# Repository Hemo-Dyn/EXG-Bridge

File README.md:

# EXG-Bridge
Ongoing development for ECG and EMG hardware interfacing with iPhones to present heartrate and muscular data

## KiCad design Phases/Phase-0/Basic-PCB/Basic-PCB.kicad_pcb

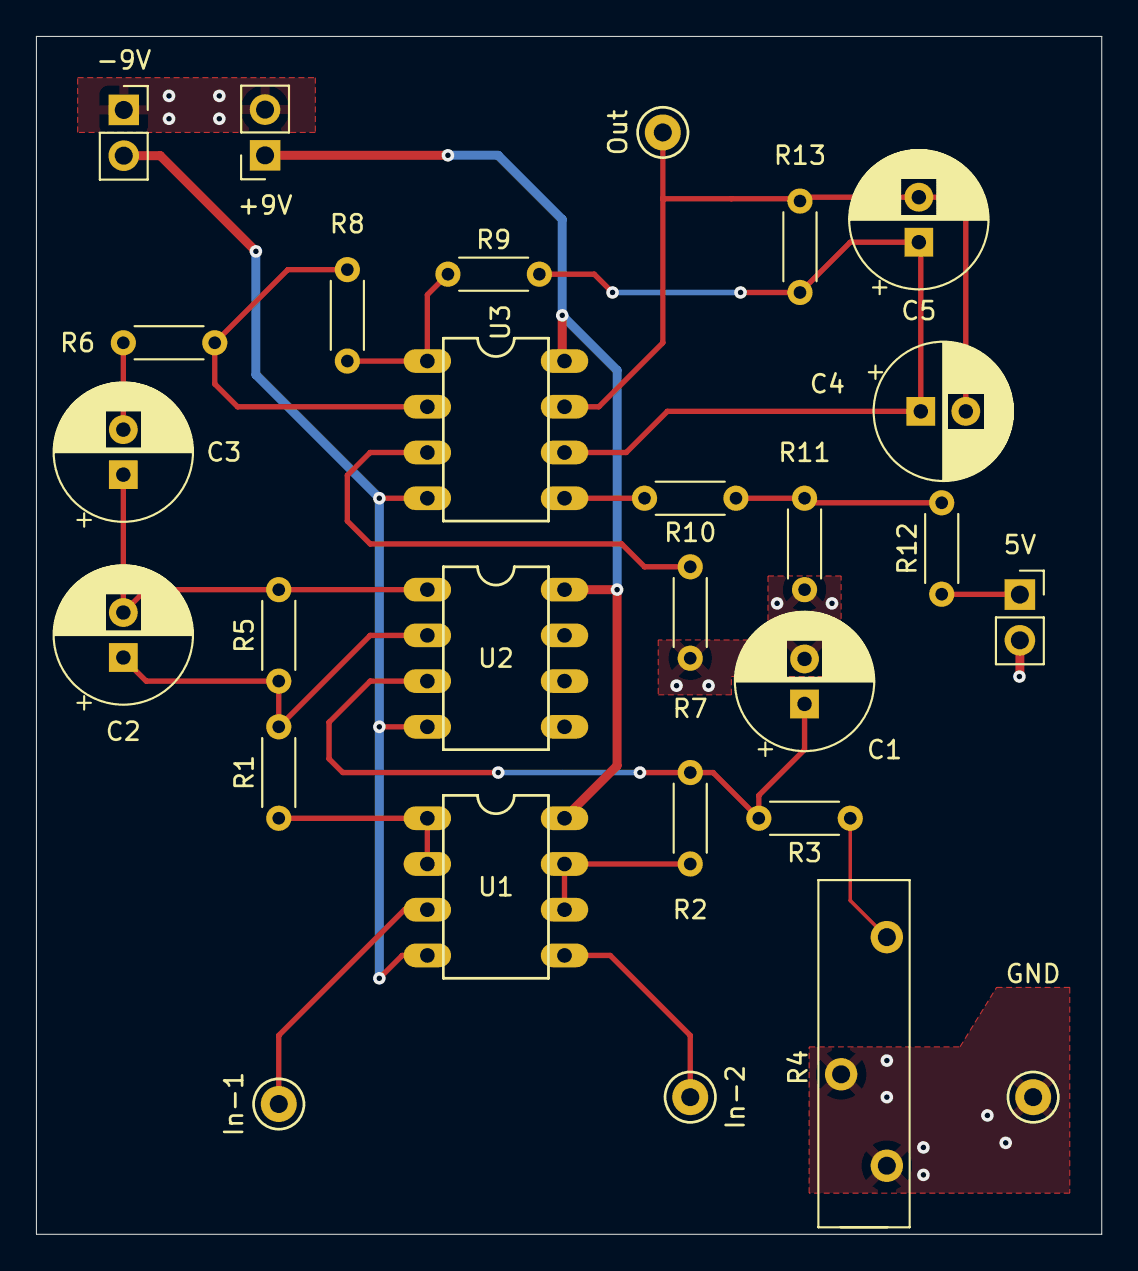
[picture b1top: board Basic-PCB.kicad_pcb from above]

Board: 2 copper layers, 59.2 x 66.5 mm, 28 parts (0 on the bottom side), 20 nets.

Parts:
5V: Conn_01x02; PinSocket_1x02_P2.54mm_Vertical
+9V: Battery; PinSocket_1x02_P2.54mm_Vertical
-9V: Battery; PinSocket_1x02_P2.54mm_Vertical
C1, C2: 470pF; CP_Radial_D7.5mm_P2.50mm
C3: 1uF; CP_Radial_D7.5mm_P2.50mm
C4: 2.2uF; CP_Radial_D7.5mm_P2.50mm
C5: 4.7nF; CP_Radial_D7.5mm_P2.50mm
GND: ELBOW; TestPoint_Keystone_5000-5004_Miniature
In-1: In1; TestPoint_Keystone_5000-5004_Miniature
In-2: In2; TestPoint_Keystone_5000-5004_Miniature
Out: output; TestPoint_Keystone_5000-5004_Miniature
R1, R2: 10k; R_Axial_DIN0204_L3.6mm_D1.6mm_P5.08mm_Horizontal
R3: 39k; R_Axial_DIN0204_L3.6mm_D1.6mm_P5.08mm_Horizontal
R4: 10k; Potentiometer_Bourns_3006P_Horizontal
R5: 47k; R_Axial_DIN0204_L3.6mm_D1.6mm_P5.08mm_Horizontal
R6: 15k; R_Axial_DIN0204_L3.6mm_D1.6mm_P5.08mm_Horizontal
R7, R8: 1M; R_Axial_DIN0204_L3.6mm_D1.6mm_P5.08mm_Horizontal
R9: 470k; R_Axial_DIN0204_L3.6mm_D1.6mm_P5.08mm_Horizontal
R10: 320; R_Axial_DIN0204_L3.6mm_D1.6mm_P5.08mm_Horizontal
R11, R12: 3.4k; R_Axial_DIN0204_L3.6mm_D1.6mm_P5.08mm_Horizontal
R13: 56k; R_Axial_DIN0204_L3.6mm_D1.6mm_P5.08mm_Horizontal
U1, U2, U3: LM358; DIL08

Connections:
+5V: 5V.1, R12.1
+9V: +9V.1 (+), U1.8 (V+), U2.8 (V+), U3.8 (V+)
-9V: -9V.2 (-), U1.4 (V-), U2.4 (V-), U3.4 (V-)
/A0: C4.2, C5.2, Out.1, R13.1, U3.7
GND: 5V.2, +9V.2 (-), -9V.1 (+), C1.2, GND.1, R4.2, R4.3, R7.1, R11.1
unnamed: C2.2, C3.1, R5.2, U2.1
unnamed: C3.2, R6.1
unnamed: In-1.1, U1.3 (+)
unnamed: In-2.1, U1.5 (+)
unnamed: R3.1, R4.1
unnamed: R8.2, R9.1, U3.1
unnamed: R10.1, R11.2, R12.2
unnamed: R1.1, U1.1, U1.2 (-)
unnamed: R2.1, U1.6 (-), U1.7
unnamed: C1.1, R2.2, R3.2, U2.3 (+)
unnamed: C2.1, R1.2, R5.1, U2.2 (-)
unnamed: R7.2, U3.3 (+)
unnamed: R6.2, R8.1, U3.2 (-)
unnamed: R10.2, U3.5 (+)
unnamed: C4.1, C5.1, R9.2, R13.2, U3.6 (-)

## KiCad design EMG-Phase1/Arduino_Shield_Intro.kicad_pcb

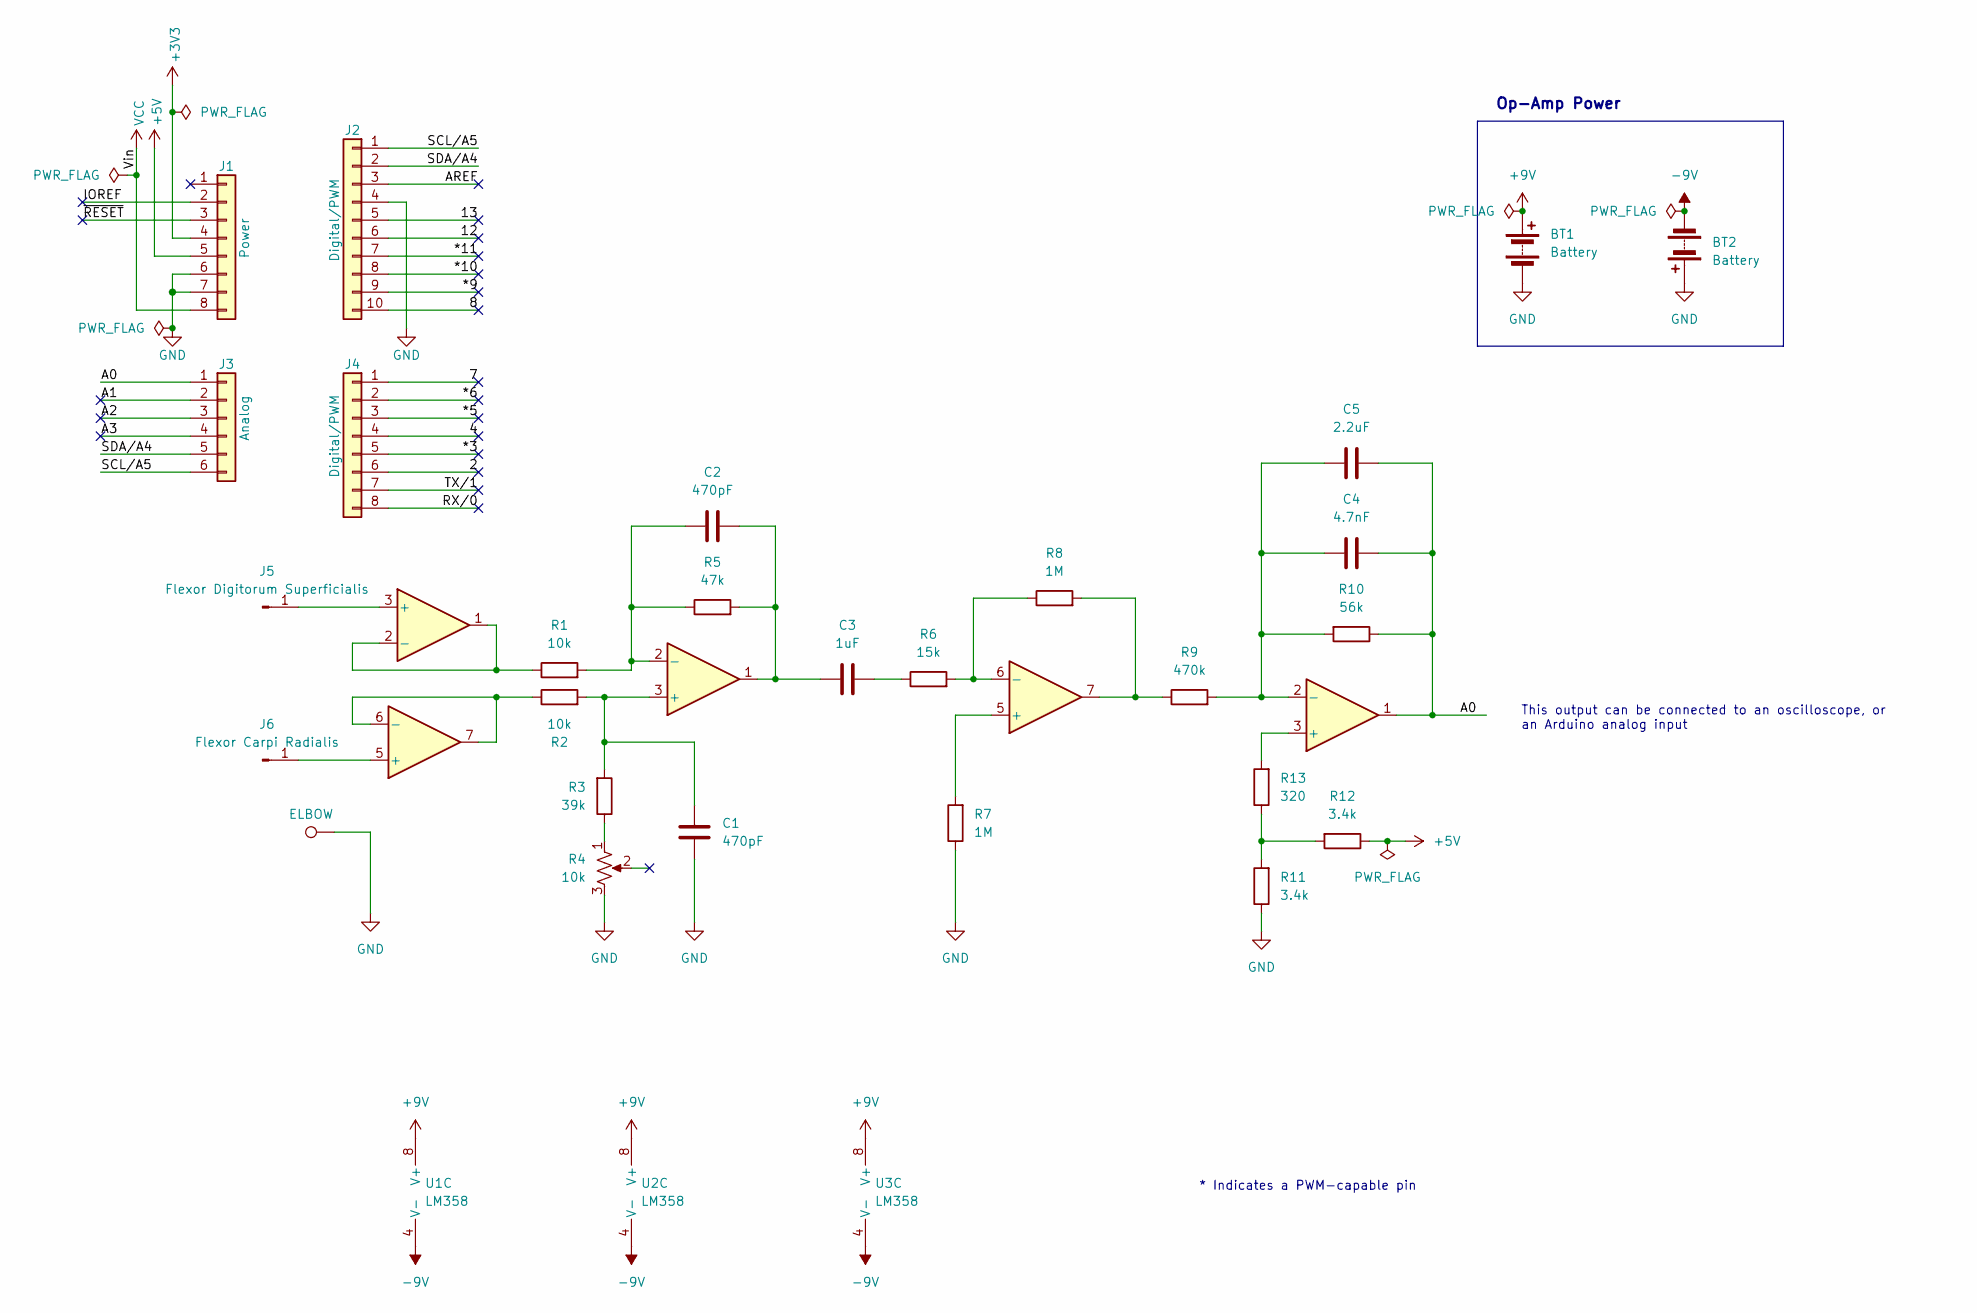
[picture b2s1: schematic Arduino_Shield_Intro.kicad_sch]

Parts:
BT1, BT2: Battery; PinSocket_1x02_P2.54mm_Vertical
C1, C2: 470pF; CP_Axial_L10.0mm_D4.5mm_P15.00mm_Horizontal
C3: 1uF; CP_Axial_L10.0mm_D4.5mm_P15.00mm_Horizontal
C4: 4.7nF; CP_Axial_L10.0mm_D4.5mm_P15.00mm_Horizontal
C5: 2.2uF; CP_Axial_L10.0mm_D4.5mm_P15.00mm_Horizontal
J1: Power; PinSocket_1x08_P2.54mm_Vertical
J2: Digital/PWM; PinSocket_1x10_P2.54mm_Vertical
J3: Analog; PinSocket_1x06_P2.54mm_Vertical
J4: Digital/PWM; PinSocket_1x08_P2.54mm_Vertical
J5: Flexor Digitorum Superficialis; TestPoint_Bridge_Pitch3.81mm_Drill1.3mm
J6: Flexor Carpi Radialis; TestPoint_Bridge_Pitch3.81mm_Drill1.3mm
R1, R2: 10k; R_Axial_DIN0204_L3.6mm_D1.6mm_P5.08mm_Horizontal
R3: 39k; R_Axial_DIN0204_L3.6mm_D1.6mm_P5.08mm_Horizontal
R4: 10k; Potentiometer_Alps_RK09K_Single_Vertical
R5: 47k; R_Axial_DIN0204_L3.6mm_D1.6mm_P5.08mm_Horizontal
R6: 15k; R_Axial_DIN0204_L3.6mm_D1.6mm_P5.08mm_Horizontal
R7, R8: 1M; R_Axial_DIN0204_L3.6mm_D1.6mm_P5.08mm_Horizontal
R9: 470k; R_Axial_DIN0204_L3.6mm_D1.6mm_P5.08mm_Horizontal
R10: 56k; R_Axial_DIN0204_L3.6mm_D1.6mm_P5.08mm_Horizontal
R11, R12: 3.4k; R_Axial_DIN0204_L3.6mm_D1.6mm_P5.08mm_Horizontal
R13: 320; R_Axial_DIN0204_L3.6mm_D1.6mm_P5.08mm_Horizontal
TP4: ELBOW; TestPoint_Bridge_Pitch3.81mm_Drill1.3mm
U1, U2, U3: LM358; DIL08

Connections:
+3V3: J1.4
+5V: J1.5, R12.1
+9V: BT1.1 (+), U1.8 (V+), U2.8 (V+), U3.8 (V+)
-9V: BT2.2 (-), U1.4 (V-), U2.4 (V-), U3.4 (V-)
/2: J4.6
/4: J4.4
/7: J4.1
/8: J2.10
/12: J2.6
/13: J2.5
/*3: J4.5
/*5: J4.3
/*6: J4.2
/*9: J2.9
/*10: J2.8
/*11: J2.7
/A0: C4.2, C5.2, J3.1, R10.1, U3.1
/A1: J3.2
/A2: J3.3
/A3: J3.4
/AREF: J2.3
/IOREF: J1.2
/RX/0: J4.8
/SCL/A5: J2.1, J3.6
/SDA/A4: J2.2, J3.5
/TX/1: J4.7
/~RESET: J1.3
GND: BT1.2 (-), BT2.1 (+), C1.2, J1.6, J1.7, J2.4, R4.3, R7.1, R11.1, TP4.1
unnamed: C2.2, C3.1, R5.2, U2.1
unnamed: C3.2, R6.1
unnamed: J5.1, U1.3 (+)
unnamed: J6.1, U1.5 (+)
unnamed: R3.1, R4.1
unnamed: R8.2, R9.1, U2.7
unnamed: R11.2, R12.2, R13.1
unnamed: R1.1, U1.1, U1.2 (-)
unnamed: R2.1, U1.6 (-), U1.7
unnamed: C1.1, R2.2, R3.2, U2.3 (+)
unnamed: C2.1, R1.2, R5.1, U2.2 (-)
unnamed: R7.2, U2.5 (+)
unnamed: R6.2, R8.1, U2.6 (-)
unnamed: R13.2, U3.3 (+)
unnamed: C4.1, C5.1, R9.2, R10.2, U3.2 (-)
VCC: J1.8

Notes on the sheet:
Op-Amp Power
* Indicates a PWM-capable pin
This output can be connected to an oscilloscope, or an Arduino analog input

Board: 2 copper layers, 34 parts (0 on the bottom side), 22 nets, no tracks yet.

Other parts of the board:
MH1, MH2, MH3, MH4: MountingHole_3.2mm

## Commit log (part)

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2025-06-11 Rename EMG-Bridge.png to images/EMG-Bridge.png
2025-06-11 Mission statement and next step Phase-1.md
2025-06-11 Rename Phase-1.md to Planning/Phase-1.md
2025-06-22 Hello, testing, blah blah
2025-06-22 adds example.txt
2025-06-29 Started the first KiCad Project
    Started first KiCad Project. Just realized it would be good to only focus on the Arduino Shield once I print this basic board out. I'd need SMD parts for the shield.
2025-08-03 PCB for Phase 0
    Made a PCB for Phase 0 bridge device.
2025-08-07 Improved Phase 0 PCB
    Made slightly more compact PCB and include op amp models
2025-09-04 Changed footprints for battery terminals
    Changed footprints for battery terminals to ones found in a Makerspace nearby
2025-09-04 Rename project from EMG-Bridge to EXG-Bridge
